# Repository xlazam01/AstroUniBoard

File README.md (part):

# AstroUniBoard

A small (35 × 42 mm) STM32G0B1 controller for the **imaging train**. It drives a focuser and a camera rotator, reads
temperature, humidity and camera roll, and has a USB hub, so the camera's USB cable runs through the board.
It is built to sit on the moving part of the train and rotate with the camera, so only one USB cable and one 12 V
cable leave the rotating side.

| | |
|---|---|
| Status | Release [v2.1.0](https://github.com/xlazam01/AstroUniBoard/releases/tag/v2.1.0) ([package notes](release/2.1.0/README.md)): HW rev 2.3 (SHT40 on the board, snap-off SHT40 sensor tab with a backup sensor slot, 0603 status LEDs), firmware V2 `2.1.0` (SHT3x / SHT4x auto-detect), protocol 2. Current ASCOM driver [0.2.1](https://github.com/xlazam01/AstroUniBoard/releases/tag/driver-v0.2.1) (pre-release). Rev 2.3 is not ordered yet and firmware 2.1.0 is not yet tested on hardware. Previous: [v2.0.0](https://github.com/xlazam01/AstroUniBoard/releases/tag/v2.0.0) (HW rev 2.1) |
| MCU | STM32G0B1CBT6, Cortex-M0+ 64 MHz, 128 KB flash, 144 KB RAM |
| Motors | 2 × TMC2209 (UART, StealthChop / SpreadCycle, StallGuard), up to 1.5 A RMS each (firmware limit) |
| Sensors | SHT40 temperature/humidity on board (+ a second SHT40 on a snap-off tab for outside the board), MPU-6000 accelerometer for camera roll |
| Host | USB-C, CDC serial, VID/PID 1209:0001 (pid.codes test PID until our own is assigned) |
| Hub | CH334P, one downstream USB-C for the camera (or a guide camera, or any other device) |
| Power | 12 V on an XT30 (motors + 5.3 V buck). Logic also runs from USB alone, without motors |
| Licences | firmware and software GPL-3.0, hardware CERN-OHL-S-2.0 |

Renders are from KiCad and show the board as JLC delivers it (DNP sockets left out).
Schematic: [docs/astrouniboard-rev2.3-schematic.pdf](docs/astrouniboard-rev2.3-schematic.pdf).

---

## Contents

- [What is on the board and why](#what-is-on-the-board-and-why)
- [Other applications](#other-applications)
- [Alternatives considered](#alternatives-considered)
- [Connectors and jumpers](#connectors-and-jumpers)
- [Bill of materials](#bill-of-materials)
- [Assembly](#assembly), including **[the J5 / XT30 order](#1-j5-before-j6-the-xt30--read-this-first)**
- [First power-up](#first-power-up)
- [Firmware](#firmware)
- [Host software](#host-software)
- [Repository layout](#repository-layout)

---

## What is on the board and why

| Feature | Part | Why it is there |
|---|---|---|
| **Two identical motor channels: focuser and rotator** | 2 × TMC2209 (U3 focuser, U2 rotator), same parts and 0.11 Ω sense on both | The same driver circuit twice, so either channel can take either job, and one BOM line covers both. **Focuser:** version 1 targets the **guide-camera focuser** behind an OAG, which N.I.N.A. cannot focus on its own (see the [Secondary Focuser plugin](https://github.com/xlazam01/SecondaryFocuser-NINA)); StallGuard can stop a move against a hard stop. **Rotator:** the firmware keeps the mechanical angle and never crosses the cable-wrap limits (default ±180°, configurable); the sky offset stays with the host. StealthChop keeps both silent and avoids vibration during exposures |
| **One UART for both drivers** | USART2, addresses 0 / 1 | Run current, hold current, microsteps and mode can be set at runtime and saved, with no pots to adjust. Driver faults, overtemperature and StallGuard are visible to the host |
| **Camera roll sensor** | MPU-6000 U10 (I²C, 0x68) | The board rotates with the camera, so the accelerometer measures camera roll against gravity. That gives **IMU homing**: the rotator finds its zero without a switch, flag or Hall sensor. Calibrate once (three captures, any mounting orientation, also upside down) |
| **Temperature / humidity** | SHT40-BD1B U8 (0x45; SHT31 on rev 2.0/2.1) | For temperature compensation of focus (done on the host) and for dew point (ASCOM ObservingConditions). It is on the board because the board sits on the optical train |
| **Switched sensor supply** | PB9 → R32 → SHT40 VDD | **Less self-heating:** the sensor sits on a board that warms up from the drivers and the buck, and a sensor that is powered all the time adds its own heat. Powering it only around a measurement keeps the reading closer to the air temperature, which matters for focus temperature compensation. (The firmware still keeps it powered and uses the switch to power-cycle a stuck sensor; duty-cycling it is a firmware option for later.) The on-board SHT40-BD1B answers at 0x45, so the **external SHT40-AD1B** (0x44) fits on the same bus. (Rev 2.0 got the same split from an SHT31 with ADDR tied to PB9.) |
| **Snap-off sensor tab** (rev 2.2) | U15 SHT40-AD1B (0x44) at the tip of a 4 × 10 mm tab on the left edge, one mouse-bite row. Rev 2.3: footprint for a backup U16 SHT40-CD1B (0x46) on the tab's bottom, DNP | The board's own sensor reads the board, not the air. Snap the tab off with pliers, wire its pads to J9 (3V3/GND on top, SDA/SCL on the bottom) and put it where the air temperature matters, for example on the dew shield. No copper pour on the tab, so it carries little heat. It is part of the same PCB and is assembled with it, so there is no second board to order. U16 is left out because fitting it makes the assembly double-sided; the firmware does not read 0x46 yet |
| **Position memory** | 24AA64 EEPROM U4 | Focuser and rotator positions survive a power cycle. A 256-slot ring with CRC spreads the wear (two writes per move). A move cut by power loss is detected and flagged "unverified" |
| **USB hub** | CH334P U6, USBLC6 ESD on both ports, CH213K current-limited switch on the downstream VBUS | One cable from the PC carries the board and the camera. The downstream port is protected against shorts and ESD. The hub is **USB 2.0 (480 Mbit/s)**: fine for a guide camera, but a USB 3 imaging camera loses speed on it and should get its own cable |
| **Power path** | XT30 J6 → F1 2 A polyfuse → D24 SMF15A TVS (rev 2.1) → ME3116 buck (5.3 V) → CH213K ideal-diode OR with USB VBUS → ME6231 3.3 V LDO | 12 V for the motors and a 5 V rail for the hub. D24 clamps the plug-in ringing of a long cable on the all-ceramic input capacitance to below the TMC2209's 29 V limit. F1 trips on a short or overload behind it and resets when cooled. There is no reverse-polarity FET: a reversed supply drives D24 forward until F1 trips, which may cost D24. Rely on the keyed XT30 and check home-made pigtails. The board also comes up from USB alone (bench work, firmware updates) while the motors stay unpowered. 5.3 V leaves headroom for the drop across the ideal diode and the downstream current switch |
| **12 V sense** (rev 2.1) | R33/R34 divider on PB10 | The firmware can see that motor power is missing or low before a move, instead of finding out from a driver that stops answering |
| **Motor supply jumper** | JP4, one 3-pad solder jumper `12V – Vdrive – 5V`, 12 V side bridged | 5 V motors can be used from USB power for light loads. One middle pad means only one source can be selected (rev 2.0 had two separate jumpers that could short 12 V onto 5 V), see [Assembly](#4-solder-jumper-jp4) |
| **Status LEDs** | D1 status (PB12), D2 activity (PB4) in 0603 (rev 2.3), D3 = 12 V present, D4 = 5 V present in 0402 | You can see power, motion and errors without a PC. The brightness is adjustable and the LEDs are dim, because the board sits next to a camera |
| **Buttons** | RST, LEFT (= BOOT0), RIGHT | RST and BOOT0 are for recovery. LEFT/RIGHT are not used by the firmware: in the Triton enclosure the board is mounted upside down and out of reach |
| **Spare I/O** | J4 Hall/index, J8 AUX1/AUX2, J9 I²C, J10 UART6 — all DNP | For other uses of the board (filter wheel index, dew heater MOSFET, GPS, SQM). See [docs/USE_CASES.md](docs/USE_CASES.md) |
| **Mounting** | 4 × M2 (29 × 29 mm) and 4 × M3 (26 × 26 mm), overlapping keyholes | Fits both standoff patterns used in the rig enclosures. The 26 × 26 mm M3 pattern is the **NEMA 14 hole pattern**, so the board also screws straight onto the back of a NEMA 14 stepper: ideal for a focuser motor or a small mount axis, with no bracket and the shortest possible motor cable |

Pin map and electrical details: [docs/HARDWARE.md](docs/HARDWARE.md).

## Other applications

The board is a general two-stepper controller with an IMU, a temperature/humidity sensor and a USB hub. Besides the
focuser + rotator it was designed for, these uses came up (details in [docs/USE_CASES.md](docs/USE_CASES.md)):

| Use | What it takes |
|---|---|
| **Dual focuser** (main + guide scope, or OAG guide camera) | Firmware only: both channels as focusers |
| **Filter wheel** | Firmware only: one channel drives the wheel, J4 Hall input as the index |
| **Motorised dust cap / flat panel** | Firmware only for the cap; the panel dimming needs PWM on AUX (J8) |
| **Small mount or star tracker** (barn door, camera-lens mount) | Both channels as RA/Dec, board mounted straight on a NEMA 14; the IMU helps with levelling. OnStepX-based, needs more flash (G0B1CC/CE) |
| **Telescope cover, roof or small dome shutter** | Light loads only (TMC2209, about 2 A peak) |
| **Mount / observatory monitor** | IMU for vibration, wind shake and "scope bumped" alarms; SHT40 for dew-point alerts |
| **Dew heater control** | PWM on AUX1/AUX2 to an external MOSFET, closed loop on the dew point |
| **GPS, sky quality meter, cloud sensor** | GPS on UART6 (J10); TSL2591 or MLX90614 on I²C (J9), as an ASCOM SafetyMonitor / ObservingConditions |
| **Non-astro** | Camera slider or pan/tilt for timelapse, microscope focus stacking, 3D-scan turntable, syringe pump or slow linear stage |

## Alternatives considered

These options were weighed during the design, with the reason for each decision. Most are recorded in more detail in
[docs/V2_PLAN.md](docs/V2_PLAN.md) §9 and [docs/adr/](docs/adr/).

| Topic | Chosen | Considered instead | Why |
|---|---|---|---|
| Firmware | Own small firmware V2 (`fw/`) | Keep the OnStepX port (`fw-onstepx/`) | OnStepX filled 93 % of flash and carried mount code and the LX200 dialect we never use. V2 uses 65 %. The OnStepX build stays for rev 1 boards and for users who want OnStep clients |
| Step generation | Hardware timer + STEP pin, exact step count | TMC2209 `VACTUAL` internal generator | VACTUAL loses the step count, and a focuser must know its position |
| Motion | One axis at a time (`ERR,8` while busy) | Both axes at once | One step timer, a simpler ISR, and there is no real need to focus and rotate at the same moment |
| Protocol | OpenWheel family `:NN…#` | LX200 / OnStep dialect | The host libraries (detection, transport, watchdog) are shared with OpenWheel. Every command gets an answer |
| Code sharing with OpenWheel | Copy & adapt | Common library or submodule | Only two devices so far; extract a library when a third one needs it ([ADR 0001](docs/adr/0001-shared-code-openwheel.md)) |
| Rotator homing | IMU gravity homing (optional at boot) | Hall sensor or limit switch on J4 | No extra parts on the rotating ring. J4 stays available for a Hall index |
| Focuser homing | None: soft limits 0…max, position kept in EEPROM, manual sync | Home switch or StallGuard homing | A focuser rarely needs a home position. Fewer moving parts and no slamming into the end stop |
| Temperature compensation | On the host (driver / N.I.N.A.) | In the firmware | The host knows the filter, the optics and the AF history. The firmware only reports the sensor data |
| ASCOM architecture | One LocalServer: Focuser + Rotator + ObservingConditions on one port | In-process DLLs | N.I.N.A., the debug app and the plugin can be connected at the same time |
| Network | USB only. Alpaca after 2.0 | Alpaca / Wi-Fi on the device | No ESP on the board. Keeps the device simple and the attack surface small |
| Power connector | XT30 (keyed, 15 A class) | 5.5/2.1 barrel jack (rev 1) | Barrel jacks fall out and short when they are plugged in. The XT30 is keyed against reverse polarity and locks firmly |
| Motor connectors | J5 horizontal JST-PH for the rotator, focuser wires soldered (J3 DNP) | Vertical JST-PH on both | Edge entry: the cable leaves in the board plane, next to the USB cables. The trade-off is the [stacking with the XT30](#1-j5-before-j6-the-xt30--read-this-first) |
| MCU | STM32G0B1CBT6 (128 KB) | G0B1CCT6 (256 KB), G0B1CET6 (512 KB), same pinout | V2 fits in 128 KB. The larger parts are drop-in replacements if stock or features need them (avoid the `…N` variants, they have a different pinout) |
| LEDs | D1/D2 0603 red (Basic, rev 2.3), D3/D4 0402 red (Extended) | All four in 0402, or all four in 0603 | Rev 2.3 moved the two status LEDs to the Basic 0603 part. D3/D4 stay 0402 for space; moving them too would save the last LED Extended fee |
| Buttons as hand controller | Not used | Manual focus in/out on LEFT/RIGHT | Not reachable in the Triton enclosure |
| Rev 3 ideas | — | 2–3 PWM dew-heater outputs, switched 12 V, INA219 power monitor, SWD pads | Would make it a focuser + rotator + hub + power box. See [docs/USE_CASES.md](docs/USE_CASES.md) |

## Connectors and jumpers

| Ref | Side | What | Pinout |
|---|---|---|---|
| J2 | top edge | USB-C **to the PC** (upstream, board + hub) | — |
| J7 | top edge | USB-C **to the camera** (downstream, hub port) | — |
| J5 | top edge, horizontal | **Rotator motor**, JST-PH 4 (S4B-PH-K) | 1 B2, 2 B1, 3 A1, 4 A2 |
| J6 | **bottom** edge, under J5 | **12 V in**, XT30PW-M (male pins on the board); F1 polyfuse and TVS D24 on top next to its pins | `+` / `−` marked on the bottom silkscreen. **Not reverse-polarity protected** |
| J3 | pads, DNP | Focuser motor (solder wires or a vertical JST-PH 4) | 1 B2 (G), 2 B1 (BK), 3 A1 (R), 4 A2 (BL): colours on the bottom silkscreen |
| J4 | pads, DNP | Hall / index input | 1 3V3, 2 GND, 3 HALL |
| J8 | pads, DNP | AUX GPIO | 1 3V3, 2 AUX1 (X1), 3 AUX2 (X2), 4 GND |
| J9 | pads, DNP | External I²C (the snap-off SHT40 tab at 0x44, plus 0x46 if U16 is fitted, or any I²C sensor) | 1 SDA, 2 SCL, 3 3V3, 4 GND |
| J11 | snap-off tab, left edge | Wire pads of the SHT40 tab (U15) | top: 3V3, GND; bottom: SDA, SCL → J9 1 SDA, 2 SCL, 3 3V3, 4 GND |
| J10 | pads, DNP | UART6 | 1 3V3, 2 TX6, 3 RX6, 4 GND |
| JP4 | top, between the XT30 pins | Motor supply (Vdrive), 3 pads `12V – Vdrive – 5V` | **12V side bridged** by default |

The motor pin order (B2 B1 A1 A2) matches common 4-wire NEMA cables. Check your motor's coil pairs with a meter:
a swapped pair makes the motor buzz instead of turning. It does not damage anything.

## Bill of materials

Rev 2.3, JLCPCB assembly. Every fitted part carries an `LCSC` field in the schematic, so the JLC fabrication toolkit
fills the BOM by itself. Snapshot 2026-11-09 (stock checked 2026-11-06). Check stock before ordering, see the notes below the table.

| Ref | Qty | Value | Package | LCSC |
|---|---|---|---|---|
| U5 | 1 | STM32G0B1CBT6 | LQFP-48 | C2847904 |
| U2, U3 | 2 | TMC2209-LA-T | QFN-28 5×5 | C2150710 |
| U6 | 1 | CH334P USB 2.0 hub | LQFN-16 3×3 | C5373042 |
| U10 | 1 | MPU-6000 | QFN-24 4×4 | C92401 |
| U8 | 1 | SHT40-BD1B-R2 (0x45) | DFN-4 1.5×1.5 | C7461849 |
| U15 | 1 | SHT40-AD1B-R2 (0x44, snap-off tab) | DFN-4 1.5×1.5 | C2909890 |
| U4 | 1 | 24AA64T-I/OT | SOT-23-5 | C2061092 |
| U12 | 1 | ME3116AM6G buck | SOT-23-6 | C97643 |
| U1 | 1 | ME6231A33M3G 3.3 V LDO | SOT-23 | C2765181 |
| U11, U13, U14 | 3 | CH213K ideal diode / current-limited switch | SOT-23 | C5456874 |
| U7, U9 | 2 | USBLC6-2SC6 ESD | SOT-23-6 | C2687116 |
| Y1 | 1 | 8 MHz crystal (TAXM8M4RDBCCT2T) | 3225 | C400090 |
| Y2 | 1 | 12 MHz crystal (TAXM12M4RDBCCT2T) | 3225 | C164041 |
| L4 | 1 | 10 µH (IHLP2020BZER100M11) | IHLP-2020 | C844984 |
| D23 | 1 | SS34 Schottky | SMA | C8678 |
| D24 | 1 | SMF15A TVS (12 V input) | SOD-123FL | C123802 |
| F1 | 1 | Polyfuse 2 A hold / 3.5 A trip, 16 V (Ruilon SMD1206P200TF/16) | 1206 | C55125664 |
| D1, D2 | 2 | LED red | 0603 | C2286 |
| D3, D4 | 2 | LED red | 0402 | C130719 |
| J2, J7 | 2 | USB-C receptacle (G-Switch GT-USB-7010ASV) | THT/SMD | C2988369 |
| J5 | 1 | JST S4B-PH-K, horizontal | THT | C265452 |
| J6 | 1 | Amass XT30PW-M | THT, **bottom** | C431092 |
| RST1, LEFT/BOOT1, RIGHT1 | 3 | TS-1088-AR02016 | SMD | C720477 |
| C2, C3, C13, C16, C36–C44 | 13 | 22 µF 25 V | 0805 | C45783 |
| C29 | 1 | 10 µF 25 V | 0805 | C15850 |
| C24, C28, C31, C32, C45–C47, C53, C59–C66 | 16 | 10 µF 10 V | 0402 | C315248 |
| C14, C48–C51 | 5 | 10 µF 6.3 V | 0402 | C15525 |
| C1, C10, C11, C33 | 4 | 1 µF | 0402 | C52923 |
| C19–C23, C25–C27, C30, C56 | 10 | 100 nF 50 V | 0402 | C307331 |
| C6, C8, C9, C12, C15, C17, C52, C54, C55, C58, C69, C70, C71 | 13 | 100 nF 16 V | 0402 | C1525 |
| C7, C18 | 2 | 22 nF 50 V | 0402 | C1532 |
| C34, C35 | 2 | 4.7 nF 50 V (USB shield) | 0402 | C1538 |
| C57 | 1 | 2.2 nF 50 V | 0402 | C1531 |
| C4, C5 | 2 | 10 pF | 0402 | C32949 |
| R10, R11, R19, R20 | 4 | 0.11 Ω (sense) | 0805 | C5126077 |
| R3, R4, R5, R9, R13, R15, R22, R24, R34 | 9 | 10 kΩ | 0402 | C25744 |
| R6, R7, R8, R14, R16, R17 | 6 | 5.1 kΩ | 0402 | C25905 |
| R21, R33 | 2 | 100 kΩ | 0402 | C25741 |
| R25, R26 | 2 | 56 kΩ | 0402 | C25796 |
| R27 | 1 | 33 kΩ | 0402 | C25779 |
| R23 | 1 | 1.78 kΩ 1 % | 0402 | C113478 |
| R12 | 1 | 1 kΩ | 0402 | C11702 |
| R18 | 1 | 510 Ω | 0402 | C25123 |
| R32 | 1 | 47 Ω | 0402 | C25118 |
| R28–R31 | 4 | 22 Ω | 0402 | C25092 |
| JP4 | — | 3-pad solder jumper, 12 V side bridged | — | — |
| **Not fitted (DNP)** | | | | |
| J3, J8, J9, J10 | 4 | JST B4B-PH-K, vertical (optional) | THT | C131334 |
| J4 | 1 | JST B3B-PH-K, vertical (optional) | THT | C131339 |
| U16 | 1 | SHT40-CD1B-R2 (0x46, backup on the tab, **bottom**) | DFN-4 1.5×1.5 | C7461852 |

Hand parts (not from JLC): XT30U-F cable plug with 16–18 AWG silicone wire, a JST PH 4-pin housing with crimped
contacts for the rotator motor, M2 or M3 standoffs.

Notes before ordering:

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
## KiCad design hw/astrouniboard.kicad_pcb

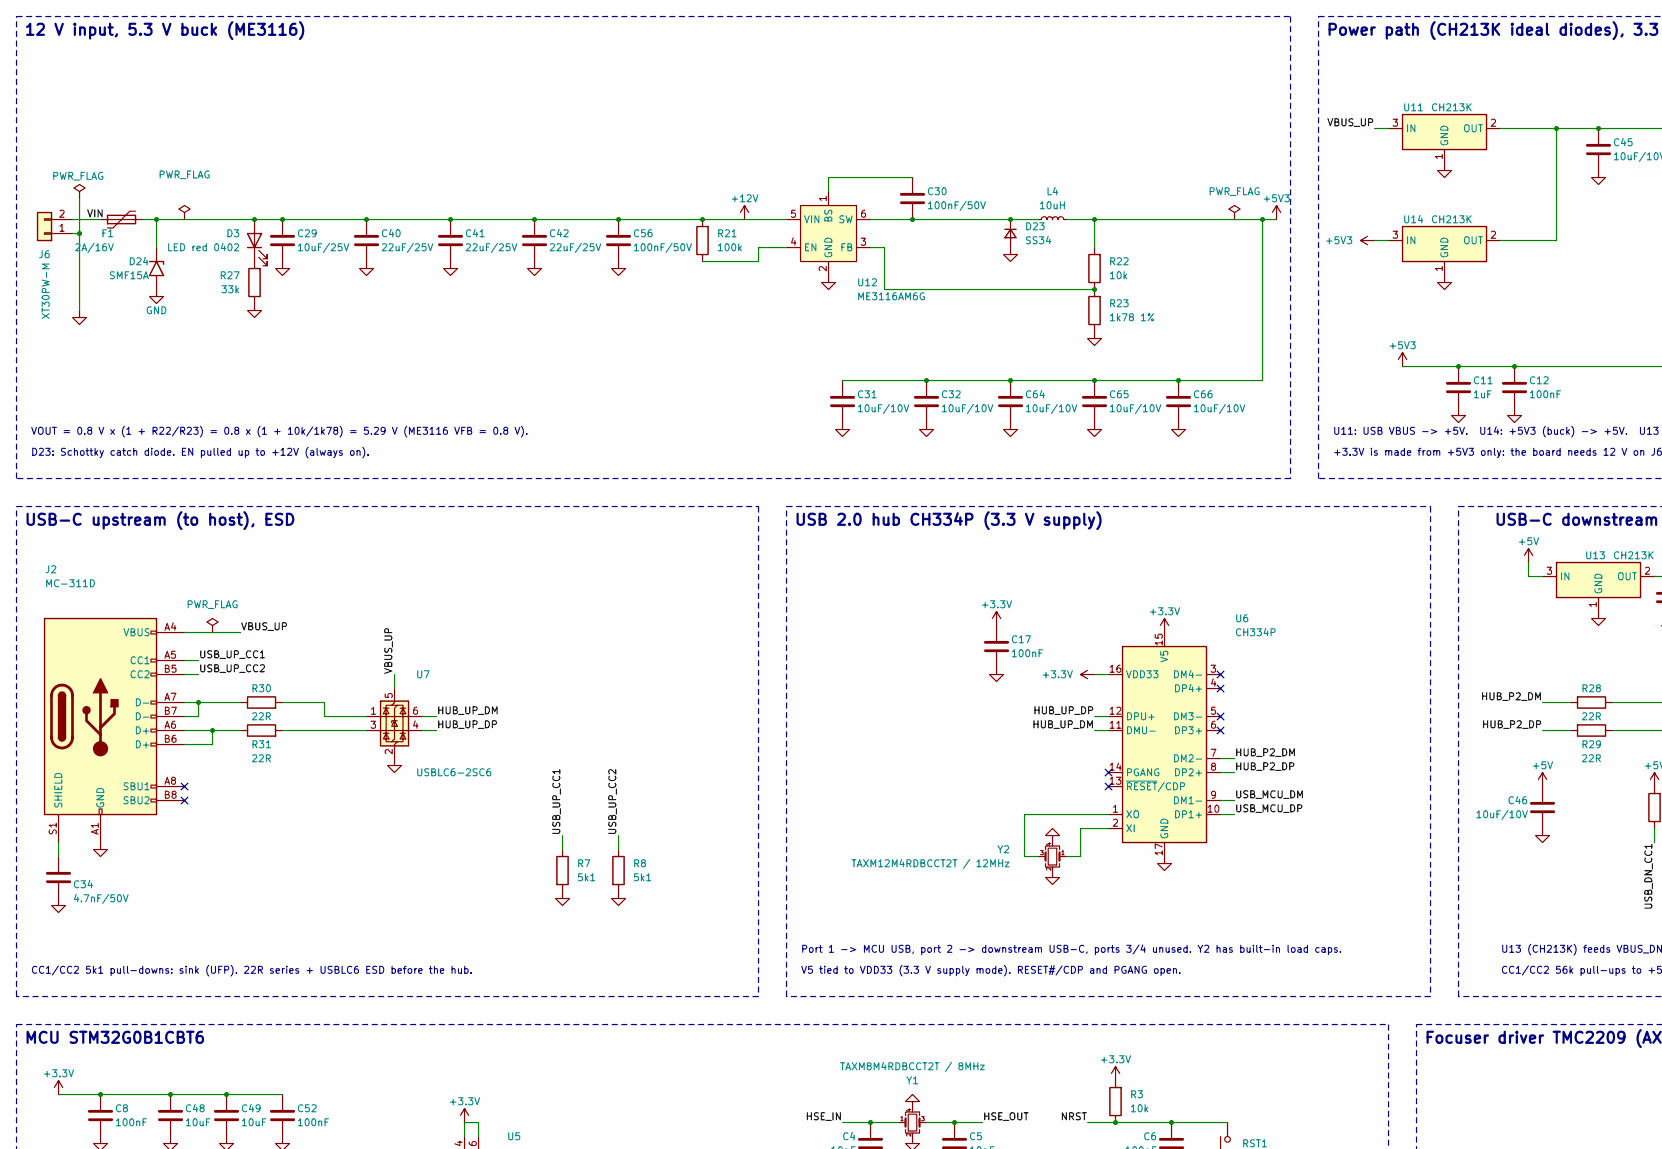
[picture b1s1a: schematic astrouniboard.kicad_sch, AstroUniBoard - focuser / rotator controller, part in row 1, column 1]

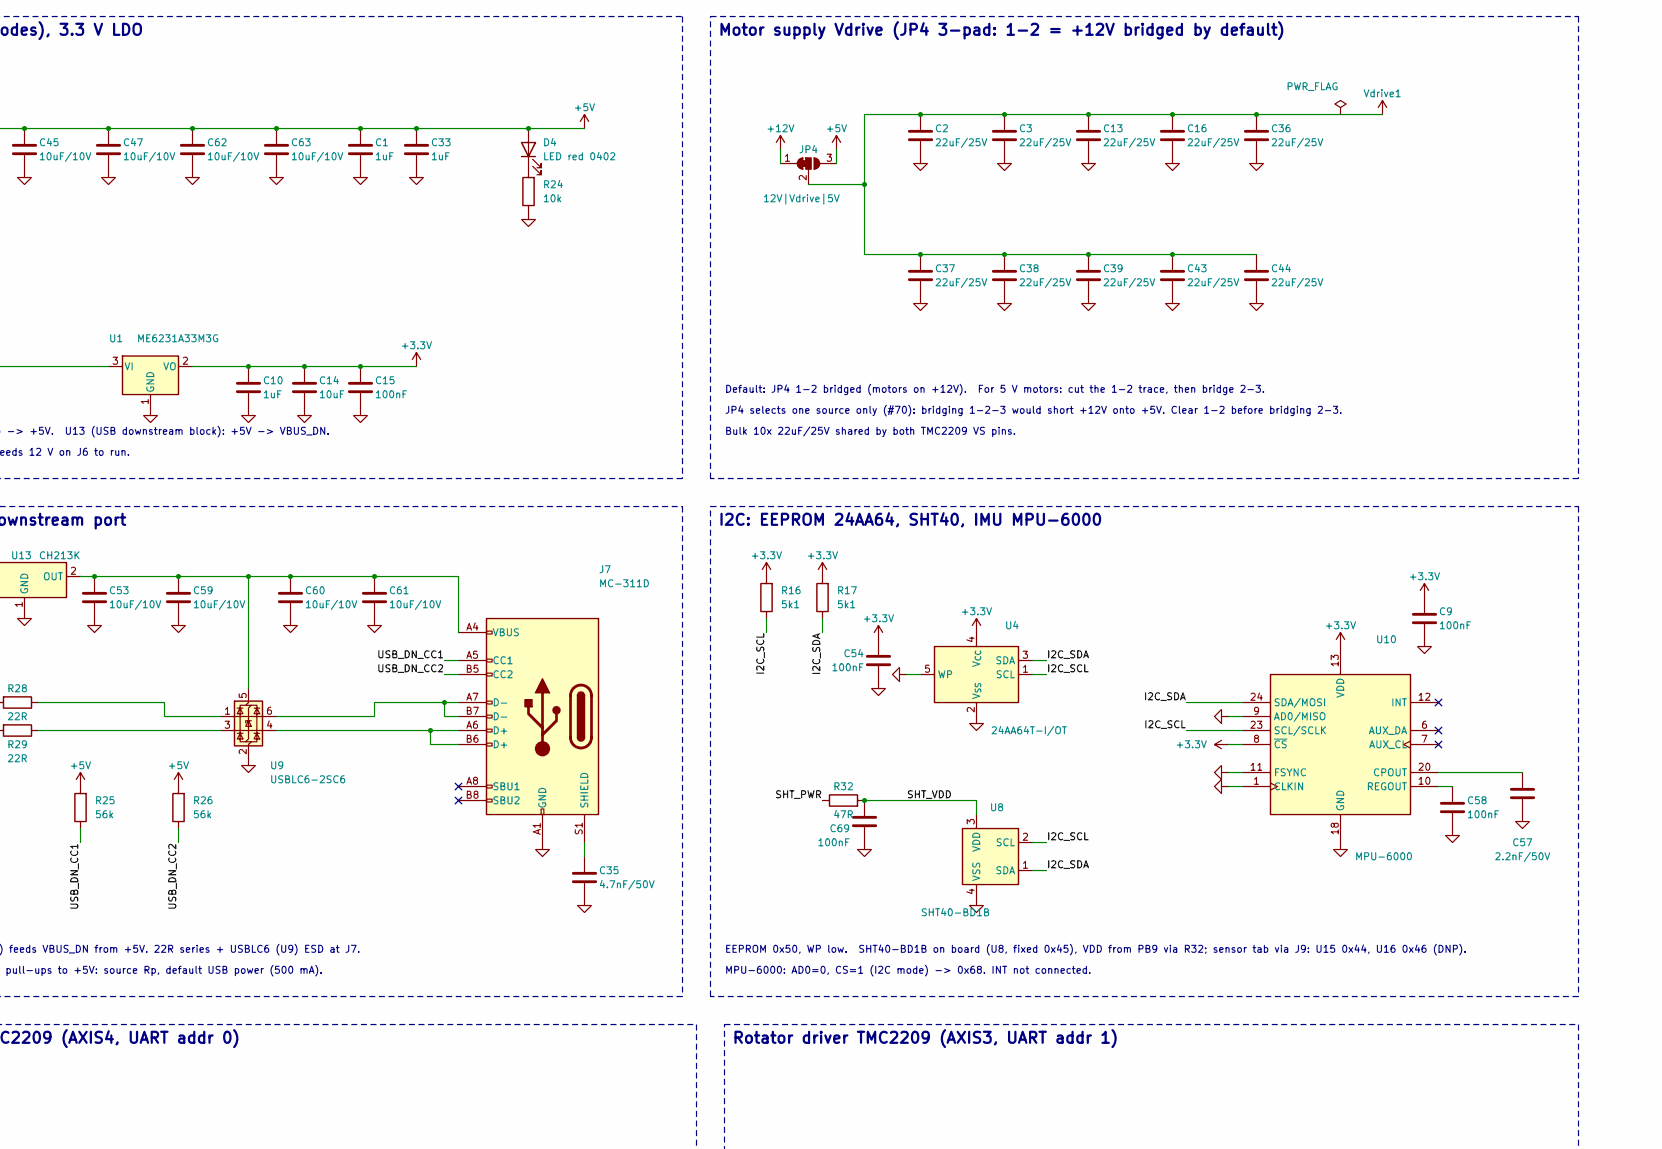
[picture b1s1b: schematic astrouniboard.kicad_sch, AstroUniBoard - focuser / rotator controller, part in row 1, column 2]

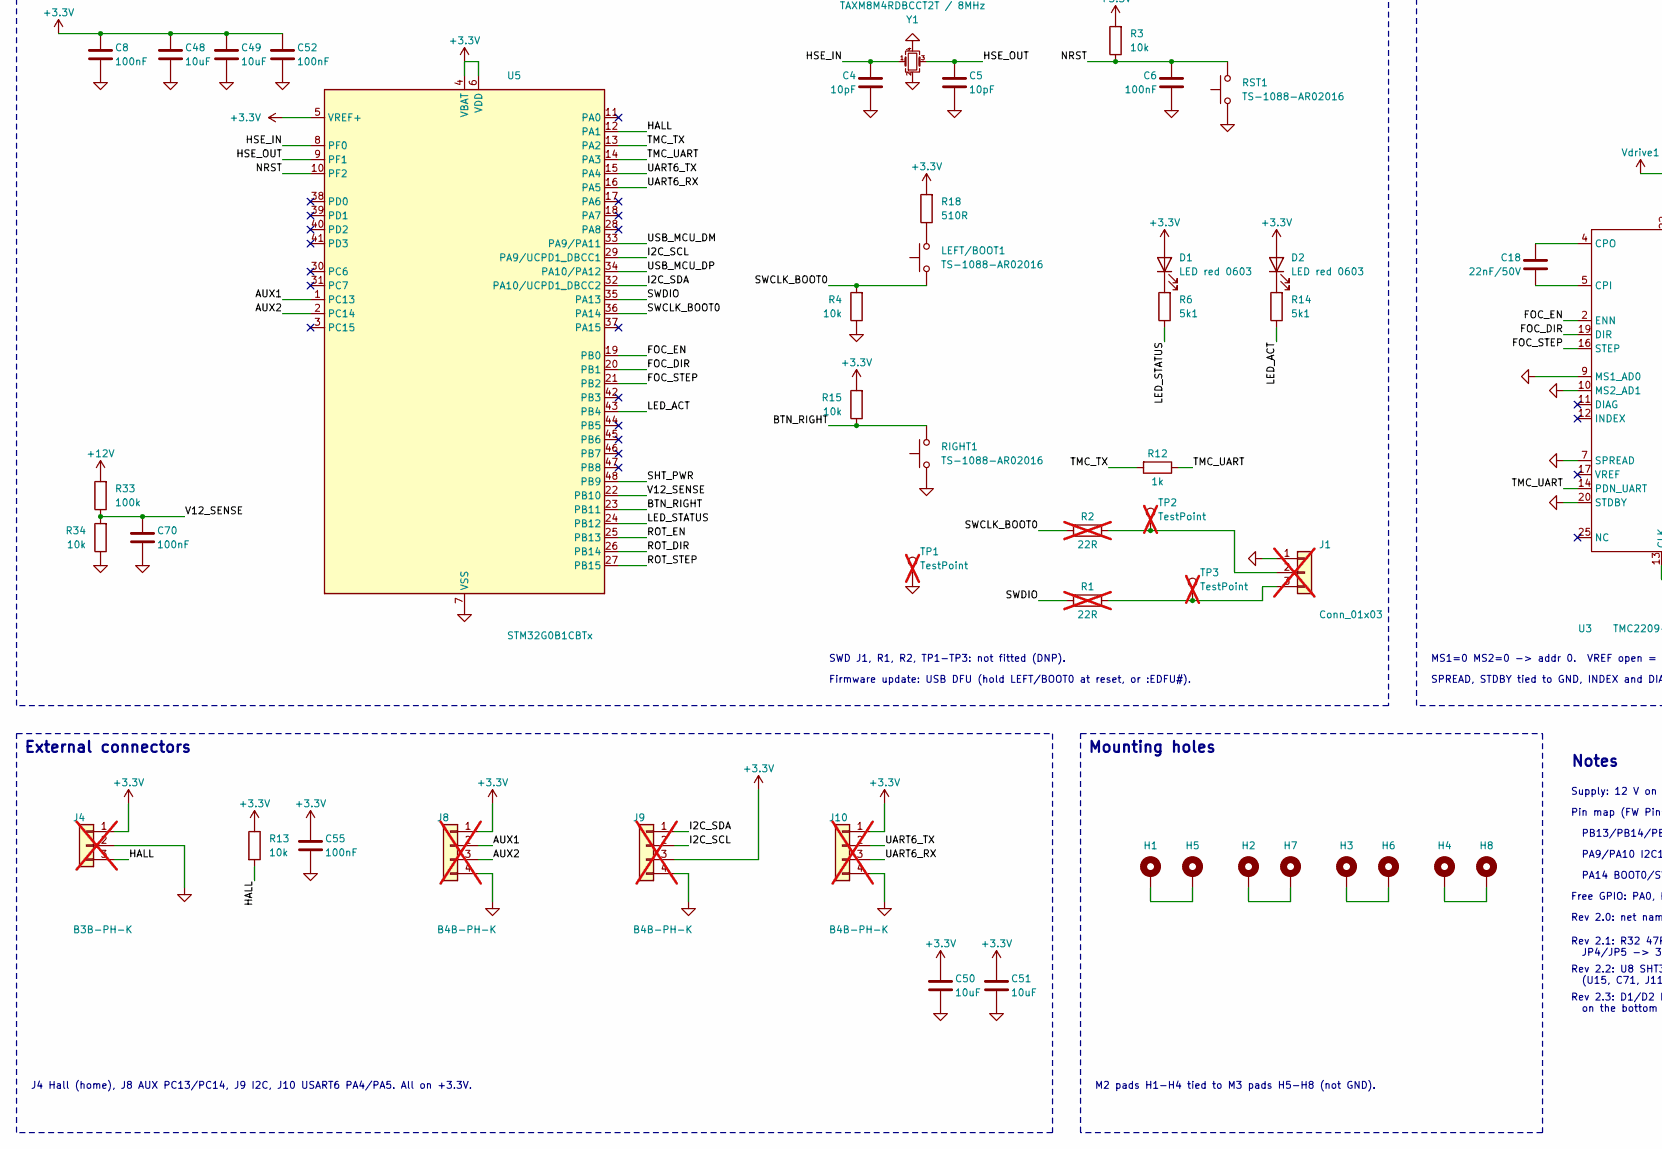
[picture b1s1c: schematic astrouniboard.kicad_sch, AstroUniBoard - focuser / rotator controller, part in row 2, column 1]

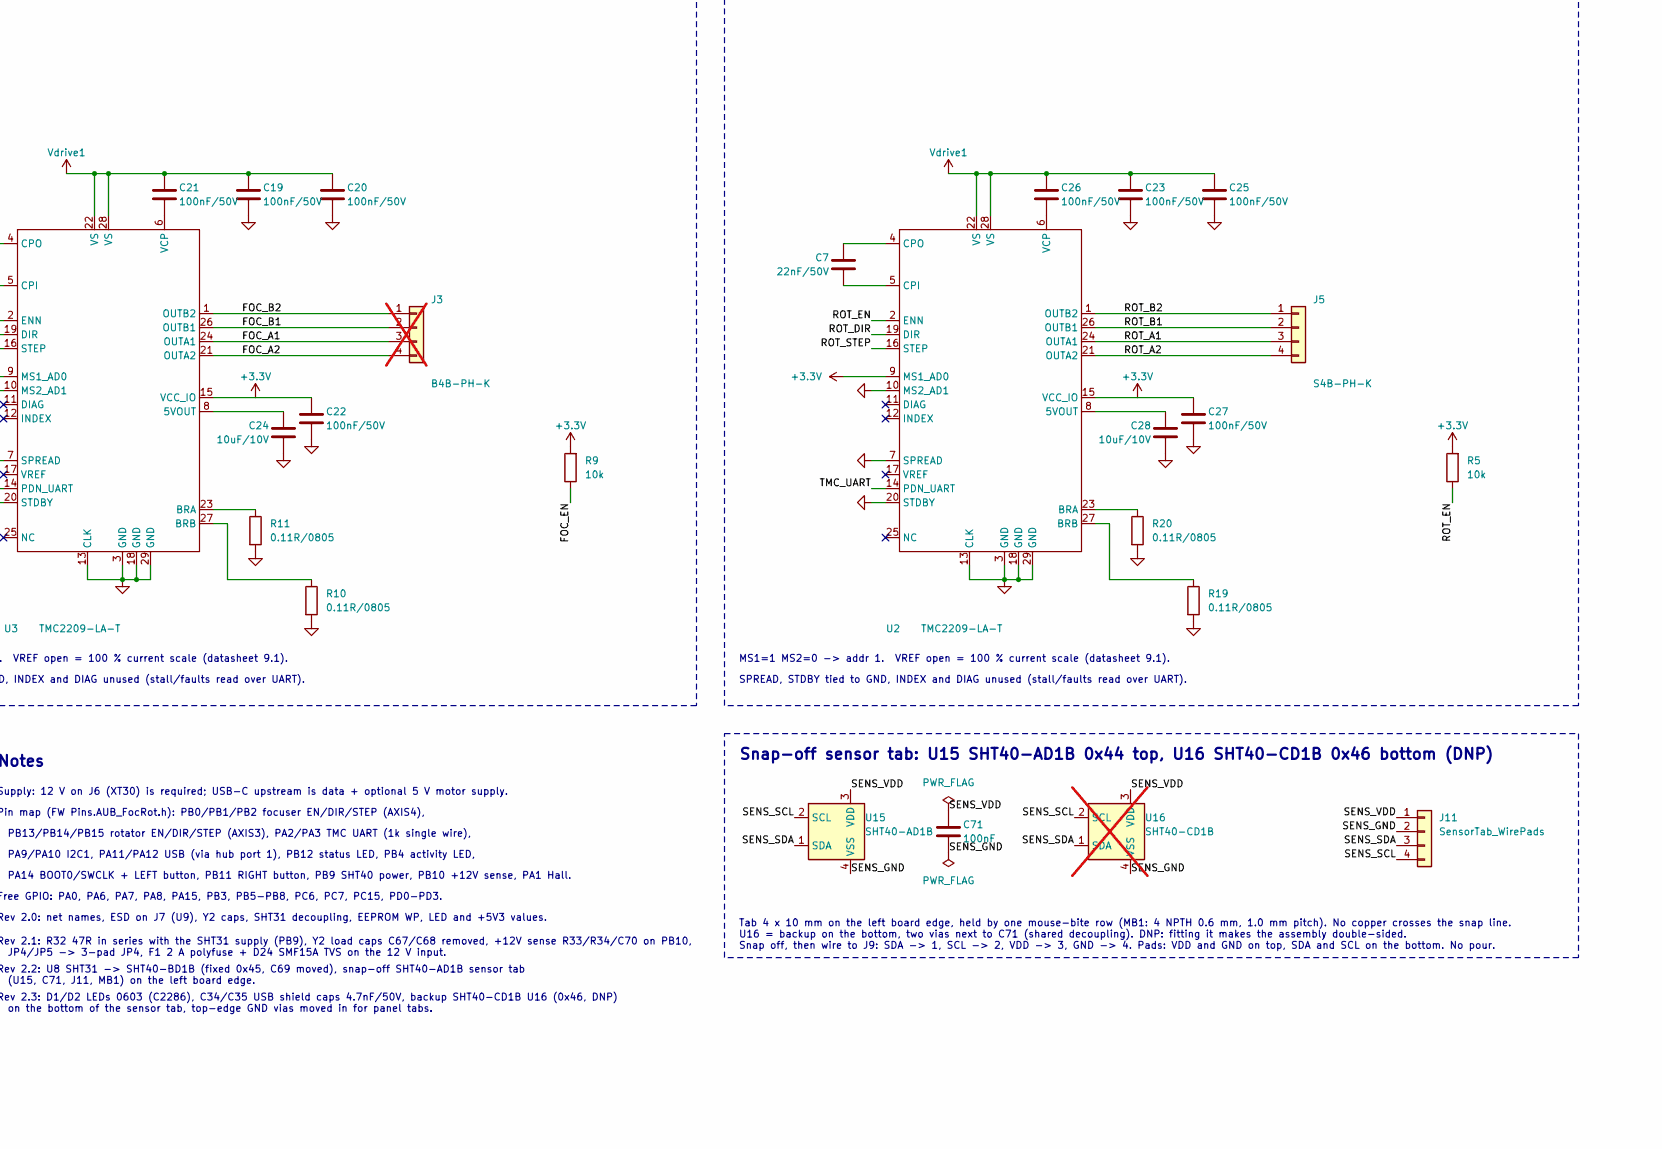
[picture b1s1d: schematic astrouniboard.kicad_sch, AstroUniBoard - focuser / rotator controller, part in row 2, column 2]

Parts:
C1, C10, C11, C33: 1uF; C_0402_1005Metric; LCSC C52923
C2, C3, C13, C16, C36, C37, C38, C39, C40, C41, C42, C43, C44: 22uF/25V; C_0805_2012Metric; LCSC C45783
C4, C5: 10pF; C_0402_1005Metric; LCSC C32949
C6, C8, C9, C12, C15, C17, C52, C54, C55, C58, C69, C70, C71: 100nF; C_0402_1005Metric; LCSC C1525
C7, C18: 22nF/50V; C_0402_1005Metric; LCSC C1532
C14, C48, C49, C50, C51: 10uF; C_0402_1005Metric; LCSC C15525
C19, C20, C21, C22, C23, C25, C26, C27, C30, C56: 100nF/50V; C_0402_1005Metric; LCSC C307331
C24, C28, C31, C32, C45, C46, C47, C53, C59, C60, C61, C62, C63, C64, C65, C66: 10uF/10V; C_0402_1005Metric; LCSC C315248
C29: 10uF/25V; C_0805_2012Metric; LCSC C15850
C34, C35: 4.7nF/50V; C_0402_1005Metric; LCSC C1538
C57: 2.2nF/50V; C_0402_1005Metric; LCSC C1531
D1, D2: LED red 0603; LED_0603_1608Metric; LCSC C2286
D3, D4: LED red 0402; LED_0402_1005Metric; LCSC C130719
D23: SS34; D_SMA; LCSC C8678
D24: SMF15A; D_SOD-123F; LCSC C123802
F1: 2A/16V; Fuse_1206_3216Metric; LCSC C55125664
H1, H2, H3, H4: MountingHole_Pad; MountingHole_2.2mm_M2_DIN965_Pad
H5, H6, H7, H8: MountingHole_Pad; MountingHole_3.2mm_M3_DIN965_Pad
J1: Conn_01x03; JST_PH_B3B-PH-K_1x03_P2.00mm_Vertical; not fitted
J2, J7: MC-311D; USB_C_Receptacle_G-Switch_GT-USB-7010ASV; LCSC C2988369
J3, J8, J9, J10: B4B-PH-K; JST_PH_B4B-PH-K_1x04_P2.00mm_Vertical; LCSC C131334; not fitted
J4: B3B-PH-K; JST_PH_B3B-PH-K_1x03_P2.00mm_Vertical; LCSC C131339; not fitted
J5: S4B-PH-K; JST_PH_S4B-PH-K_1x04_P2.00mm_Horizontal; LCSC C265452
J6: XT30PW-M; AMASS_XT30PW-M_1x02_P2.50mm_Horizontal; LCSC C431092
J11: SensorTab_WirePads; SensorTab_WirePads_2Top_2Bottom
JP4: 12V|Vdrive|5V; SolderJumper-3_P1.3mm_Bridged12_RoundedPad1.0x1.5mm
L4: 10uH; L_5.5x5.1mm; LCSC C844984
LEFT/BOOT1: TS-1088-AR02016; SW_Push_SPST_NO_Alps_SKRK; LCSC C720477
R1, R2: 22R; R_0402_1005Metric; not fitted
R3, R4, R5, R9, R13, R15, R22, R24, R34: 10k; R_0402_1005Metric; LCSC C25744
R6, R7, R8, R14, R16, R17: 5k1; R_0402_1005Metric; LCSC C25905
R10, R11, R19, R20: 0.11R/0805; R_0805_2012Metric; LCSC C5126077
R12: 1k; R_0402_1005Metric; LCSC C11702
R18: 510R; R_0402_1005Metric; LCSC C25123
R21, R33: 100k; R_0402_1005Metric; LCSC C25741
R23: 1k78 1%; R_0402_1005Metric; LCSC C113478
R25, R26: 56k; R_0402_1005Metric; LCSC C25796
R27: 33k; R_0402_1005Metric; LCSC C25779
R28, R29, R30, R31: 22R; R_0402_1005Metric; LCSC C25092
R32: 47R; R_0402_1005Metric; LCSC C25118
RIGHT1: TS-1088-AR02016; SW_Push_SPST_NO_Alps_SKRK; LCSC C720477
RST1: TS-1088-AR02016; SW_Push_SPST_NO_Alps_SKRK; LCSC C720477
TP1, TP2, TP3: TestPoint; TestPoint_Micro; not fitted
U1: ME6231A33M3G; SOT-23; LCSC C2765181
U2, U3: TMC2209-LA-T; QFN-28-1EP_5x5mm_P0.5mm_EP3.75x3.75mm_ThermalVias; LCSC C2150710
U4: 24AA64T-I/OT; SOT-23-5; LCSC C2061092
U5: STM32G0B1CBTx; LQFP-48_7x7mm_P0.5mm; LCSC C2847904
U6: CH334P; LQFN-16-1EP_3x3mm_P0.5mm_EP1.7x1.7mm; LCSC C5373042
U7, U9: USBLC6-2SC6; SOT-23-6; LCSC C2687116
U8: SHT40-BD1B; Sensirion_DFN-4_1.5x1.5mm_P0.8mm_SHT4x_NoCentralPad; LCSC C7461849
U10: MPU-6000; InvenSense_QFN-24_4x4mm_P0.5mm; LCSC C92401
U11, U13, U14: CH213K; SOT-23; LCSC C5456874
U12: ME3116AM6G; SOT-23-6; LCSC C97643
U15: SHT40-AD1B; Sensirion_DFN-4_1.5x1.5mm_P0.8mm_SHT4x_NoCentralPad; LCSC C2909890
U16: SHT40-CD1B; Sensirion_DFN-4_1.5x1.5mm_P0.8mm_SHT4x_NoCentralPad; LCSC C7461852; not fitted
Y1: TAXM8M4RDBCCT2T / 8MHz; Crystal_SMD_3225-4Pin_3.2x2.5mm; LCSC C400090
Y2: TAXM12M4RDBCCT2T / 12MHz; Crystal_SMD_3225-4Pin_3.2x2.5mm; LCSC C164041

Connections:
+3.3V: C8.1, C9.1, C10.1, C14.1, C15.1, C17.2, C22.1, C27.2, C48.1, C49.1, C50.1, C51.1, C52.1, C54.1, C55.1, D1.2 (A), D2.2 (A), J4.1, J8.1, J9.3, J10.1, R3.2, R5.2, R9.2, R13.1, R15.2, R16.2, R17.2, R18.2, U1.2 (VO), U2.9 (MS1_AD0), U2.15 (VCC_IO), U3.15 (VCC_IO), U4.4 (V_{CC}), U5.4 (VBAT), U5.5 (VREF+), U5.6 (VDD), U6.15 (V5), U6.16 (VDD33), U10.8 (~CS), U10.13 (VDD)
+5V: C1.2, C33.2, C45.1, C46.1, C47.1, C62.1, C63.1, D4.2 (A), JP4.3 (B), R25.2, R26.2, U11.2 (OUT), U13.3 (IN), U14.2 (OUT)
+5V3: C11.1, C12.1, C31.1, C32.1, C64.1, C65.1, C66.1, L4.2, R22.2, U1.3 (VI), U14.3 (IN)
+12V: C29.1, C40.2, C41.2, C42.2, C56.1, D3.2 (A), D24.1 (A1), F1.2, JP4.1 (A), R21.2, R33.2, U12.5 (VIN)
/AUX1: J8.2, U5.1 (PC13)
/AUX2: J8.3, U5.2 (PC14)
/BTN_RIGHT: R15.1, RIGHT1.2, U5.23 (PB11)
/FOC_A1: J3.3, U3.24 (OUTA1)
/FOC_A2: J3.4, U3.21 (OUTA2)
/FOC_B1: J3.2, U3.26 (OUTB1)
/FOC_B2: J3.1, U3.1 (OUTB2)
/FOC_DIR: U3.19 (DIR), U5.20 (PB1)
/FOC_EN: R9.1, U3.2 (ENN), U5.19 (PB0)
/FOC_STEP: U3.16 (STEP), U5.21 (PB2)
/HALL: J4.3, R13.2, U5.12 (PA1)
/HSE_IN: C4.1, U5.8 (PF0), Y1.1
/HSE_OUT: C5.1, U5.9 (PF1), Y1.3
/HUB_P2_DM: R28.2, U6.7 (DM2-)
/HUB_P2_DP: R29.2, U6.8 (DP2+)
/HUB_UP_DM: U6.11 (DMU-), U7.6 (I/O1)
/HUB_UP_DP: U6.12 (DPU+), U7.4 (I/O2)
/I2C_SCL: J9.2, R16.1, U4.1 (SCL), U5.29 (PA9/UCPD1_DBCC1), U8.2 (SCL), U10.23 (SCL/SCLK)
/I2C_SDA: J9.1, R17.1, U4.3 (SDA), U5.32 (PA10/UCPD1_DBCC2), U8.1 (SDA), U10.24 (SDA/MOSI)
/LED_ACT: R14.1, U5.43 (PB4)
/LED_STATUS: R6.1, U5.24 (PB12)
/NRST: C6.1, R3.1, RST1.2, U5.10 (PF2)
/ROT_A1: J5.3, U2.24 (OUTA1)
/ROT_A2: J5.4, U2.21 (OUTA2)
/ROT_B1: J5.2, U2.26 (OUTB1)
/ROT_B2: J5.1, U2.1 (OUTB2)
/ROT_DIR: U2.19 (DIR), U5.26 (PB14)
/ROT_EN: R5.1, U2.2 (ENN), U5.25 (PB13)
/ROT_STEP: U2.16 (STEP), U5.27 (PB15)
/SENS_GND: C71.2, J11.2, U15.4 (VSS), U16.4 (VSS)
/SENS_SCL: J11.4, U15.2 (SCL), U16.2 (SCL)
/SENS_SDA: J11.3, U15.1 (SDA), U16.1 (SDA)
/SENS_VDD: C71.1, J11.1, U15.3 (VDD), U16.3 (VDD)
/SHT_PWR: R32.1, U5.48 (PB9)
/SHT_VDD: C69.1, R32.2, U8.3 (VDD)
/SWCLK_BOOT0: LEFT/BOOT1.1, R2.2, R4.2, U5.36 (PA14)
/SWDIO: R1.2, U5.35 (PA13)
/TMC_TX: R12.2, U5.13 (PA2)
/TMC_UART: R12.1, U2.14 (PDN_UART), U3.14 (PDN_UART), U5.14 (PA3)
/UART6_RX: J10.3, U5.16 (PA5)
/UART6_TX: J10.2, U5.15 (PA4)
/USB_DN_CC1: J7.A5 (CC1), R25.1
/USB_DN_CC2: J7.B5 (CC2), R26.1
/USB_MCU_DM: U5.33 (PA9/PA11), U6.9 (DM1-)
/USB_MCU_DP: U5.34 (PA10/PA12), U6.10 (DP1+)
/USB_UP_CC1: J2.A5 (CC1), R7.1
/USB_UP_CC2: J2.B5 (CC2), R8.1
/V12_SENSE: C70.1, R33.1, R34.2, U5.22 (PB10)
/VBUS_UP: J2.A4 (VBUS), J2.A9 (VBUS), J2.B4 (VBUS), J2.B9 (VBUS), U7.5 (VBUS), U11.3 (IN)
/VIN: F1.1, J6.2
GND: C1.1, C2.1, C3.1, C4.2, C5.2, C6.2, C8.2, C9.2, C10.2, C11.2, C12.2, C13.2, C14.2, C15.2, C16.2, C17.1, C19.1, C20.1, C22.2, C23.1, C24.1, C25.1, C27.1, C28.1, C29.2, C31.2, C32.2, C33.1, C34.2, C35.2, C36.1, C37.1, C38.1, C39.1, C40.1, C41.1, C42.1, C43.1, C44.1, C45.2, C46.2, C47.2, C48.2, C49.2, C50.2, C51.2, C52.2, C53.2, C54.2, C55.2, C56.2, C57.2, C58.2, C59.2, C60.2, C61.2, C62.2, C63.2, C64.2, C65.2, C66.2, C69.2, C70.2, D23.2 (A), D24.2 (A2), J1.1, J2.A1 (GND), J2.A12 (GND), J2.B1 (GND), J2.B12 (GND), J4.2, J6.1, J7.A1 (GND), J7.A12 (GND), J7.B1 (GND), J7.B12 (GND), J8.4, J9.4, J10.4, R4.1, R7.2, R8.2, R10.2, R11.2, R19.2, R20.2, R23.1, R24.1, R27.1, R34.1, RIGHT1.1, RST1.1, TP1.1, U1.1 (GND), U2.3 (GND), U2.7 (SPREAD), U2.10 (MS2_AD1), U2.13 (CLK), U2.18 (GND), U2.20 (STDBY), U2.29 (GND), U3.3 (GND), U3.7 (SPREAD), U3.9 (MS1_AD0), U3.10 (MS2_AD1), U3.13 (CLK), U3.18 (GND), U3.20 (STDBY), U3.29 (GND), U4.2 (V_{SS}), U4.5 (WP), U5.7 (VSS), U6.17 (GND), U7.2 (GND), U8.4 (VSS), U9.2 (GND), U10.1 (CLKIN), U10.9 (AD0/MISO), U10.11 (FSYNC), U10.18 (GND), U11.1 (GND), U12.2 (GND), U13.1 (GND), U14.1 (GND), Y1.2, Y1.4, Y2.2, Y2.4
unnamed: D1.1 (K), R6.2
unnamed: D2.1 (K), R14.2
unnamed: D3.1 (K), R27.2
unnamed: D4.1 (K), R24.2
unnamed: C30.2, D23.1 (K), L4.1, U12.6 (SW)
unnamed: H1.1 (1_1), H5.1 (1_1)
unnamed: H2.1 (1_1), H7.1 (1_1)
unnamed: H3.1 (1_1), H6.1 (1_1)
unnamed: H4.1 (1_1), H8.1 (1_1)
unnamed: J1.2, R2.1, TP2.1
unnamed: J1.3, R1.1, TP3.1
unnamed: J2.A6 (D+), J2.B6 (D+), R31.1
unnamed: J2.A7 (D-), J2.B7 (D-), R30.1
unnamed: C34.1, J2.S1 (SHIELD)
unnamed: J7.A6 (D+), J7.B6 (D+), U9.4 (I/O2)
unnamed: J7.A7 (D-), J7.B7 (D-), U9.6 (I/O1)
unnamed: C35.1, J7.S1 (SHIELD)
unnamed: LEFT/BOOT1.2, R18.1
unnamed: R28.1, U9.1 (I/O1)
unnamed: R29.1, U9.3 (I/O2)
unnamed: R30.2, U7.1 (I/O1)
unnamed: R31.2, U7.3 (I/O2)
unnamed: C28.2, U2.8 (5VOUT)
unnamed: R20.1, U2.23 (BRA)
unnamed: R19.1, U2.27 (BRB)
unnamed: C7.1, U2.5 (CPI)
unnamed: C7.2, U2.4 (CPO)
unnamed: C26.2, U2.6 (VCP)
unnamed: C24.2, U3.8 (5VOUT)
unnamed: R11.1, U3.23 (BRA)
unnamed: R10.1, U3.27 (BRB)
unnamed: C18.1, U3.5 (CPI)
unnamed: C18.2, U3.4 (CPO)
unnamed: C21.2, U3.6 (VCP)
unnamed: U6.2 (XI), Y2.1
unnamed: U6.1 (XO), Y2.3
unnamed: C57.1, U10.20 (CPOUT)
unnamed: C58.1, U10.10 (REGOUT)
unnamed: C30.1, U12.1 (BS)
unnamed: R21.1, U12.4 (EN)
unnamed: R22.1, R23.2, U12.3 (FB)
unnamed: C53.1, C59.1, C60.1, C61.1, J7.A4 (VBUS), J7.A9 (VBUS), J7.B4 (VBUS), J7.B9 (VBUS), U9.5 (VBUS), U13.2 (OUT)
Vdrive1: C2.2, C3.2, C13.1, C16.1, C19.2, C20.2, C21.1, C23.2, C25.2, C26.1, C36.2, C37.2, C38.2, C39.2, C43.2, C44.2, JP4.2 (C), U2.22 (VS), U2.28 (VS), U3.22 (VS), U3.28 (VS)

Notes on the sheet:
External connectors
SPREAD, STDBY tied to GND, INDEX and DIAG unused (stall/faults read over UART).
MS1=1 MS2=0 -> addr 1. VREF open = 100 % current scale (datasheet 9.1).
Rev 2.3: D1/D2 LEDs 0603 (C2286), C34/C35 USB shield caps 4.7nF/50V, backup SHT40-CD1B U16 (0x46, DNP) on the bottom of the sensor tab, top-edge GND vias moved in for panel tabs.
J4 Hall (home), J8 AUX PC13/PC14, J9 I2C, J10 USART6 PA4/PA5. All on +3.3V.
Motor supply Vdrive (JP4 3-pad: 1-2 = +12V bridged by default)
Power path (CH213K ideal diodes), 3.3 V LDO
Rotator driver TMC2209 (AXIS3, UART addr 1)
Mounting holes
I2C: EEPROM 24AA64, SHT40, IMU MPU-6000
Snap-off sensor tab: U15 SHT40-AD1B 0x44 top, U16 SHT40-CD1B 0x46 bottom (DNP)
Notes
MS1=0 MS2=0 -> addr 0. VREF open = 100 % current scale (datasheet 9.1).
U13 (CH213K) feeds VBUS_DN from +5V. 22R series + USBLC6 (U9) ESD at J7.
Focuser driver TMC2209 (AXIS4, UART addr 0)
PA9/PA10 I2C1, PA11/PA12 USB (via hub port 1), PB12 status LED, PB4 activity LED,
Pin map (FW Pins.AUB_FocRot.h): PB0/PB1/PB2 focuser EN/DIR/STEP (AXIS4),
MPU-6000: AD0=0, CS=1 (I2C mode) -> 0x68. INT not connected.
12 V input, 5.3 V buck (ME3116)
U11: USB VBUS -> +5V. U14: +5V3 (buck) -> +5V. U13 (USB downstream block): +5V -> VBUS_DN.
USB-C upstream (to host), ESD
PB13/PB14/PB15 rotator EN/DIR/STEP (AXIS3), PA2/PA3 TMC UART (1k single wire),
EEPROM 0x50, WP low. SHT40-BD1B on board (U8, fixed 0x45), VDD from PB9 via R32; sensor tab via J9: U15 0x44, U16 0x46 (DNP).
CC1/CC2 5k1 pull-downs: sink (UFP). 22R series + USBLC6 ESD before the hub.
Tab 4 x 10 mm on the left board edge, held by one mouse-bite row (MB1: 4 NPTH 0.6 mm, 1.0 mm pitch). No copper crosses the snap line. U16 = backup on the bottom, two vias next to C71 (shared decoupling). DNP: fitting it makes the assembly double-sided. Snap off, then wire to J9: SDA -> 1, SCL -> 2,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
Port 1 -> MCU USB, port 2 -> downstream USB-C, ports 3/4 unused. Y2 has built-in load caps.
JP4 selects one source only (#70): bridging 1-2-3 would short +12V onto +5V. Clear 1-2 before bridging 2-3.
Supply: 12 V on J6 (XT30) is required; USB-C upstream is data + optional 5 V motor supply.
Default: JP4 1-2 bridged (motors on +12V). For 5 V motors: cut the 1-2 trace, then bridge 2-3.
Rev 2.1: R32 47R in series with the SHT31 supply (PB9), Y2 load caps C67/C68 removed, +12V sense R33/R34/C70 on PB10, JP4/JP5 -> 3-pad JP4, F1 2 A polyfuse + D24 SMF15A TVS on the 12 V input.
Rev 2.2: U8 SHT31 -> SHT40-BD1B (fixed 0x45, C69 moved), snap-off SHT40-AD1B sensor tab (U15, C71, J11, MB1) on the left board edge.
PA14 BOOT0/SWCLK + LEFT button, PB11 RIGHT button, PB9 SHT40 power, PB10 +12V sense, PA1 Hall.
D23: Schottky catch diode. EN pulled up to +12V (always on).
M2 pads H1-H4 tied to M3 pads H5-H8 (not GND).
Bulk 10x 22uF/25V shared by both TMC2209 VS pins.
USB-C downstream port
Free GPIO: PA0, PA6, PA7, PA8, PA15, PB3, PB5-PB8, PC6, PC7, PC15, PD0-PD3.
SWD J1, R1, R2, TP1-TP3: not fitted (DNP).
MCU STM32G0B1CBT6
Rev 2.0: net names, ESD on J7 (U9), Y2 caps, SHT31 decoupling, EEPROM WP, LED and +5V3 values.

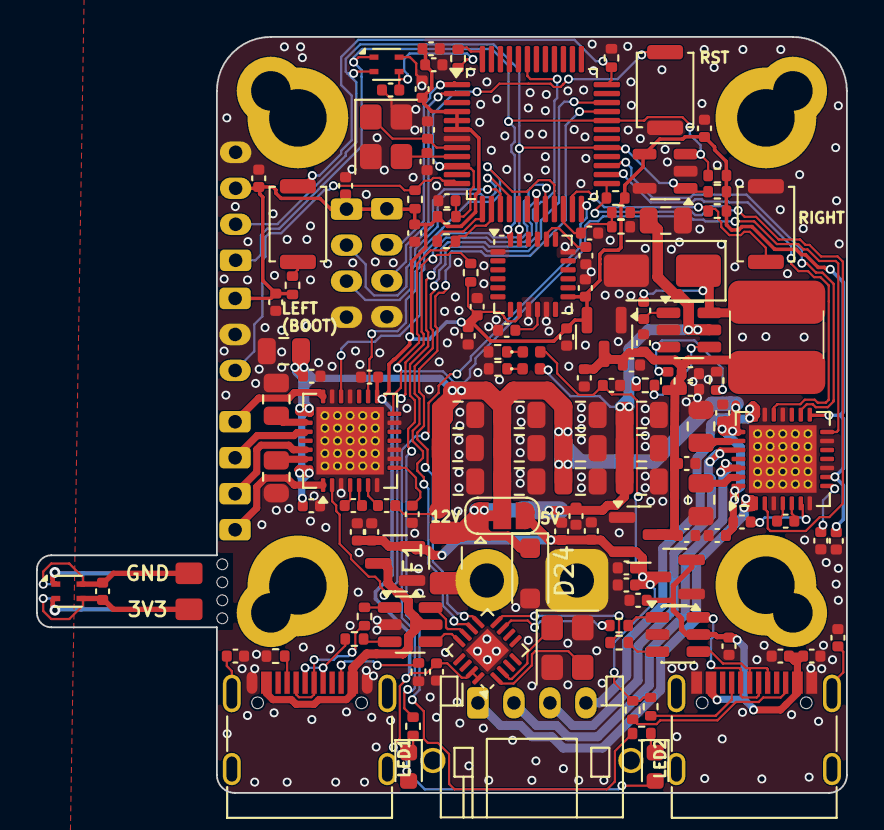
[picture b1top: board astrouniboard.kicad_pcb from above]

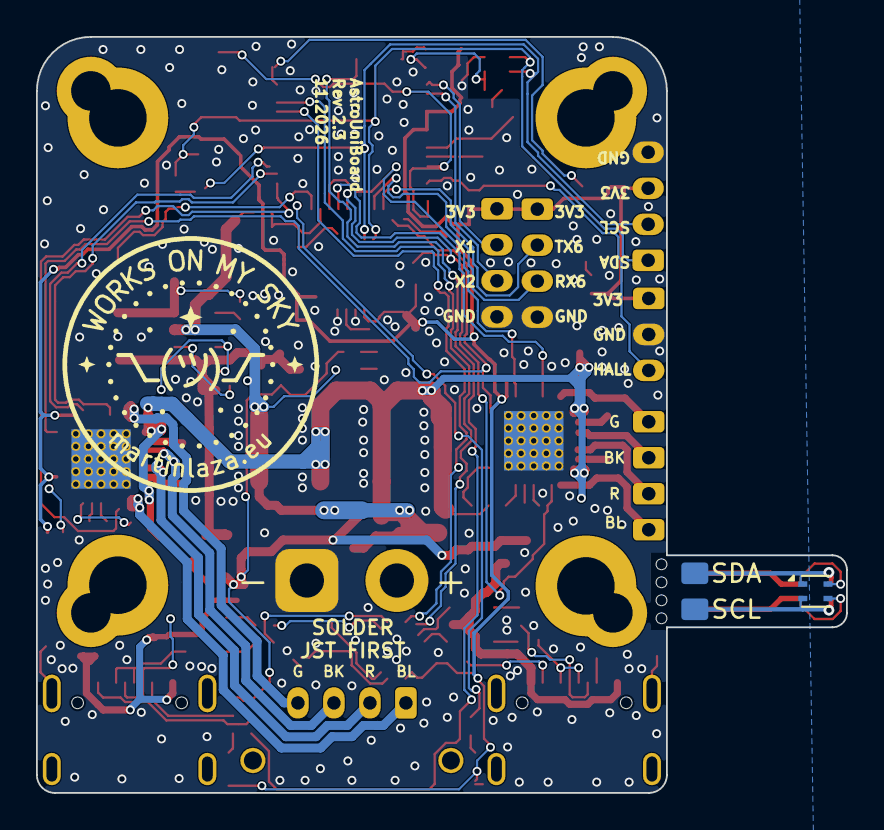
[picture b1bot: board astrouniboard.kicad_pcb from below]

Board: 2 copper layers, 45.0 x 42.0 mm, 151 parts (3 on the bottom side), 95 nets.

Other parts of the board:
LOGO1: Logo_WorksOnMySky_14mm
MB1: MouseBites; MouseBites_4x0.6mm_P1.0mm

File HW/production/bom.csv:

Designator,Footprint,Quantity,Value,LCSC Part #
"C1, C10, C11, C33",0402,4,1uF,
"C12, C15, C17, C8, C9",0402,5,100nF,
"C13, C16, C29",0805,3,10u/25V,
"C14, C31, C32",0402,3,10uF,
"C18, C7",0402,2,22n/50V,
"C19, C20, C21, C22, C23, C25, C26, C27, C30",0402,9,100n/50V,
"C2, C3",0805,2,10uF/25V,
"C24, C28",0402,2,10uF/10V,
"C4, C5",0402,2,10pF,
C6,0402,1,100n,
"D1, D2, D3, D4",0603,4,LED RED 0603,
D23,D_SMA,1,D_Small,
"F1, F2",0603,2,SMD0603P050TF,
"H1, H2, H3, H4",MountingHole_2.2mm_M2_DIN965_Pad,4,MountingHole_Pad,
"H5, H6, H7, H8",MountingHole_3.2mm_M3_DIN965_Pad,4,MountingHole_Pad,
"J10, J3, J5, J8, J9",JST_PH_B4B-PH-K_1x04_P2.00mm_Vertical,5,Conn_01x04,
"J2, J7",USB_C_Receptacle_G-Switch_GT-USB-7010ASV,2,MC-311D,
J4,JST_PH_B3B-PH-K_1x03_P2.00mm_Vertical,1,Conn_01x03,
J6,BarrelJack_GCT_DCJ200-10-A_Horizontal,1,5.5/2.1 Barell DC2,
L4,L_5.5x5.1mm,1,L_Small,
"LEFT/BOOT1, RIGHT1, RST1",SW_Push_SPST_NO_Alps_SKRK,3,TS-1088-AR02016,
"R1, R2",0402,2,22R,
"R10, R11, R19, R20",0805,4,0.11R/0805,
"R12, R24",0402,2,1k,
"R13, R15, R27, R3, R4, R5, R9",0402,7,10k,
"R14, R18, R6",0402,3,510R,
"R16, R17, R7, R8",0402,4,5k1,
R21,0402,1,100k,
R22,0402,1,6k34(10k7),
R23,0402,1,2k,
"R25, R26",0402,2,22k,
"TP1, TP2, TP3",TestPoint_Micro,3,TestPoint,
U1,SOT-23,1,ME6231,
U12,SOT-23-6,1,ME3116,
"U2, U3",QFN-28-1EP_5x5mm_P0.5mm_EP3.75x3.75mm_ThermalVias,2,~,
U4,SOT-23-5,1,24AA64T-I/OT,
U5,LQFP-48_7x7mm_P0.5mm,1,STM32G0B1CBTx,
U6,LQFN-16-1EP_3x3mm_P0.5mm_EP1.7x1.7mm,1,CH334P,
U8,Sensirion_DFN-8-1EP_2.5x2.5mm_P0.5mm_EP1.1x1.7mm,1,SHT31A-DIS,
Y1,Crystal_SMD_3225-4Pin_3.2x2.5mm,1,TAXM8M4RDBCCT2T / 8MHz,
Y2,Crystal_SMD_3225-4Pin_3.2x2.5mm,1,TAXM12M4RDBCCT2T / 12MHz,

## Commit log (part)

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2026-03-21 gitignore: exclude KiCad lock and auto-save files
2026-04-02 reorg
    new HW V2 first comit

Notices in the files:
README.md:
Licence and credits:
- Firmware and software (`fw/`, `fw-onstepx/`, `driver/`): GPL-3.0, see [LICENSE](LICENSE).
- Hardware (`hw/`): CERN-OHL-S-2.0, see [LICENSE-HARDWARE](LICENSE-HARDWARE).
- `fw-onstepx/` is derived from [OnStepX](https://github.com/hjd1964/OnStepX) by Howard Dutton and contributors.
- Sibling project, same protocol family: [OpenWheel](https://github.com/xlazam01/OpenWheel) filter wheel.
